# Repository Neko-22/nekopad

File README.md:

# Legally Distinct Catpad
Created for Hack Club Hackpad
## BOM
- 20x Cherry MX style switches
- 20x 1N418 THT Diodes
- 2x 4.7kOhm THT Resistors
- 1x I2C SSD1306 0.91" 128x32 OLED Display
- 1x XIAO RP2040 Microcontroller THT
- 1x Bottom Case (3D Print)
- 1x Top Case (3D Print)
- 1x Plate (Acryllic Laser Cut)
- 4x M3 screws
## Notes
This was hell ngl. I am absolutely *awful* at electronics design, and combine that with the joys of Linux software compatability regarding Fusion 360, I have lost so much sleep over this. I honestly think the firmware was the easiest part of this, and that's saying something.

10/10 experience would do again.

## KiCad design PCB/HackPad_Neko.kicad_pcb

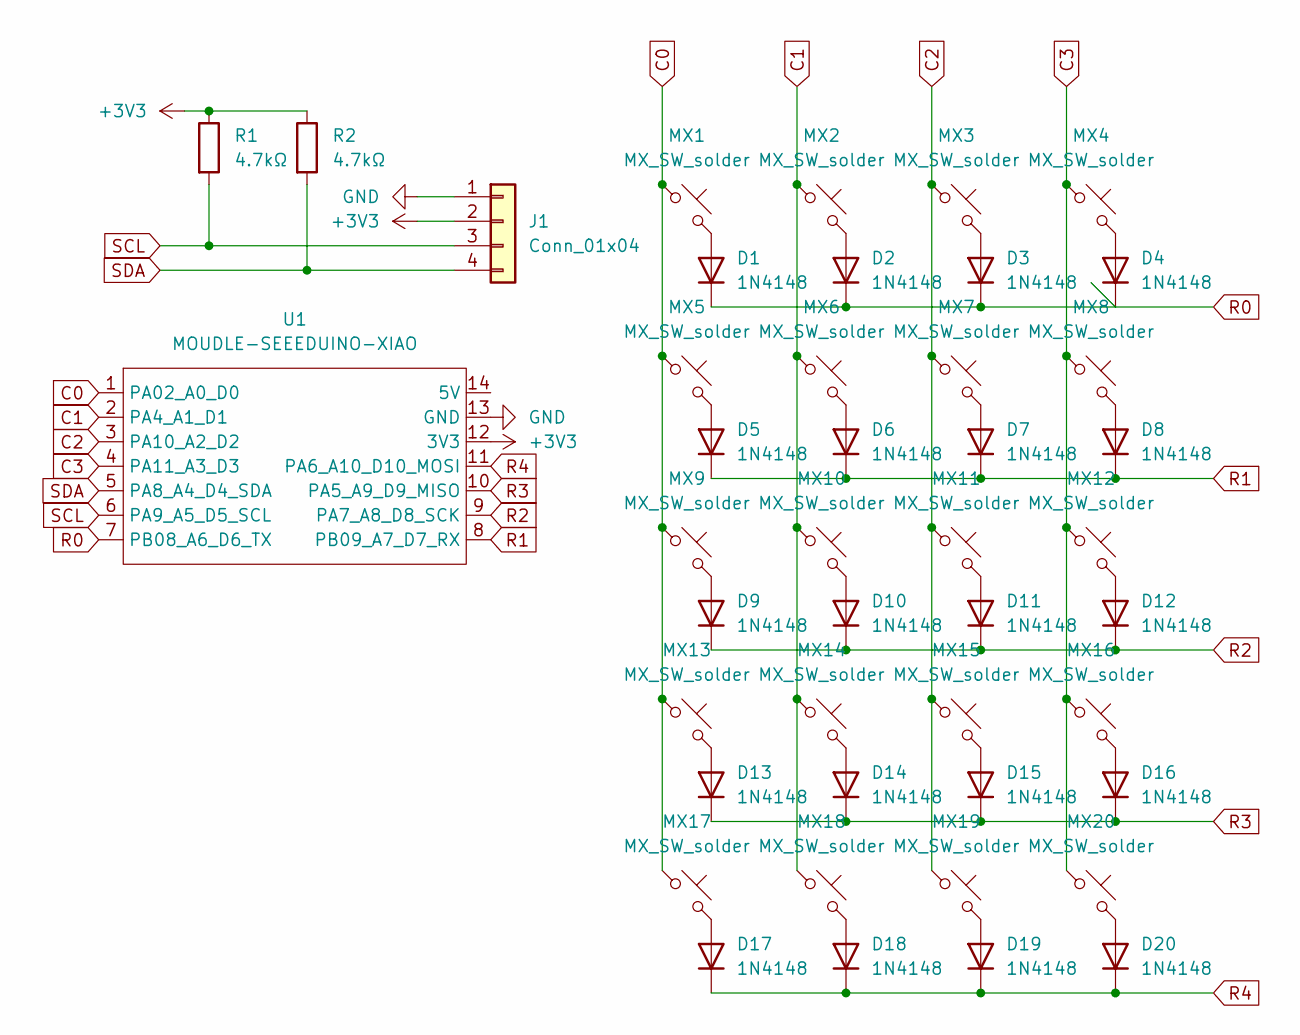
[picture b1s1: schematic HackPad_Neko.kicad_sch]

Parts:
D1, D2, D3, D4, D5, D6, D7, D8, D9, D10, D11, D12, D13, D14, D15, D16, D17, D18, D19, D20: 1N4148; D_DO-35_SOD27_P7.62mm_Horizontal
J1: Conn_01x04; SSD1306-0.91-OLED-4pin-128x32
MX1, MX2, MX3, MX4, MX5, MX6, MX7, MX8, MX9, MX10, MX11, MX12, MX13, MX14, MX15, MX16, MX17, MX18, MX19, MX20: MX_SW_solder; SW_Cherry_MX_1.00u_PCB
R1, R2: 4.7kΩ; R_Axial_DIN0204_L3.6mm_D1.6mm_P5.08mm_Horizontal
U1: MOUDLE-SEEEDUINO-XIAO; MOUDLE14P-2.54-21X17.8MM

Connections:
+3V3: J1.2, R1.1, R2.1, U1.12 (3V3)
C0: MX1.1, MX5.1, MX9.1, MX13.1, MX17.1, U1.1 (PA02_A0_D0)
C1: MX2.1, MX6.1, MX10.1, MX14.1, MX18.1, U1.2 (PA4_A1_D1)
C2: MX3.1, MX7.1, MX11.1, MX15.1, MX19.1, U1.3 (PA10_A2_D2)
C3: MX4.1, MX8.1, MX12.1, MX16.1, MX20.1, U1.4 (PA11_A3_D3)
GND: J1.1, U1.13 (GND)
unnamed: D1.2 (A), MX1.2
unnamed: D2.2 (A), MX2.2
unnamed: D3.2 (A), MX3.2
unnamed: D4.2 (A), MX4.2
unnamed: D5.2 (A), MX5.2
unnamed: D6.2 (A), MX6.2
unnamed: D7.2 (A), MX7.2
unnamed: D8.2 (A), MX8.2
unnamed: D9.2 (A), MX9.2
unnamed: D10.2 (A), MX10.2
unnamed: D11.2 (A), MX11.2
unnamed: D12.2 (A), MX12.2
unnamed: D13.2 (A), MX13.2
unnamed: D14.2 (A), MX14.2
unnamed: D15.2 (A), MX15.2
unnamed: D16.2 (A), MX16.2
unnamed: D17.2 (A), MX17.2
unnamed: D18.2 (A), MX18.2
unnamed: D19.2 (A), MX19.2
unnamed: D20.2 (A), MX20.2
R0: D1.1 (K), D2.1 (K), D3.1 (K), D4.1 (K), U1.7 (PB08_A6_D6_TX)
R1: D5.1 (K), D6.1 (K), D7.1 (K), D8.1 (K), U1.8 (PB09_A7_D7_RX)
R2: D9.1 (K), D10.1 (K), D11.1 (K), D12.1 (K), U1.9 (PA7_A8_D8_SCK)
R3: D13.1 (K), D14.1 (K), D15.1 (K), D16.1 (K), U1.10 (PA5_A9_D9_MISO)
R4: D17.1 (K), D18.1 (K), D19.1 (K), D20.1 (K), U1.11 (PA6_A10_D10_MOSI)
SCL: J1.3, R1.2, U1.6 (PA9_A5_D5_SCL)
SDA: J1.4, R2.2, U1.5 (PA8_A4_D4_SDA)

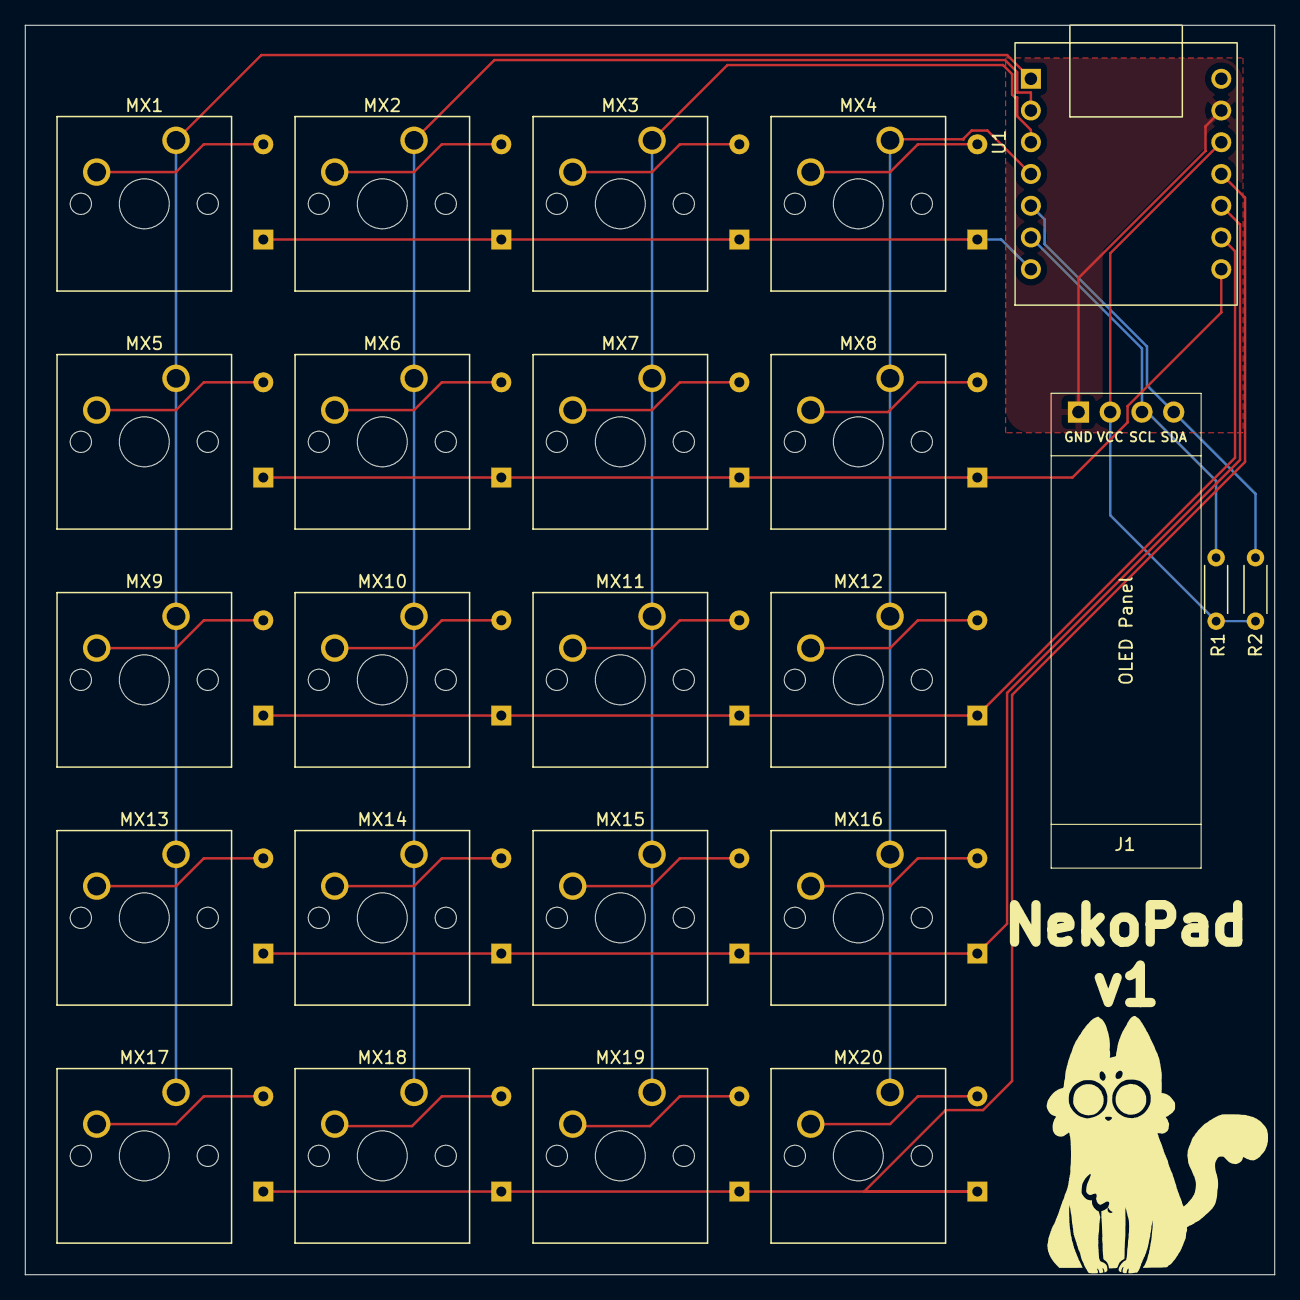
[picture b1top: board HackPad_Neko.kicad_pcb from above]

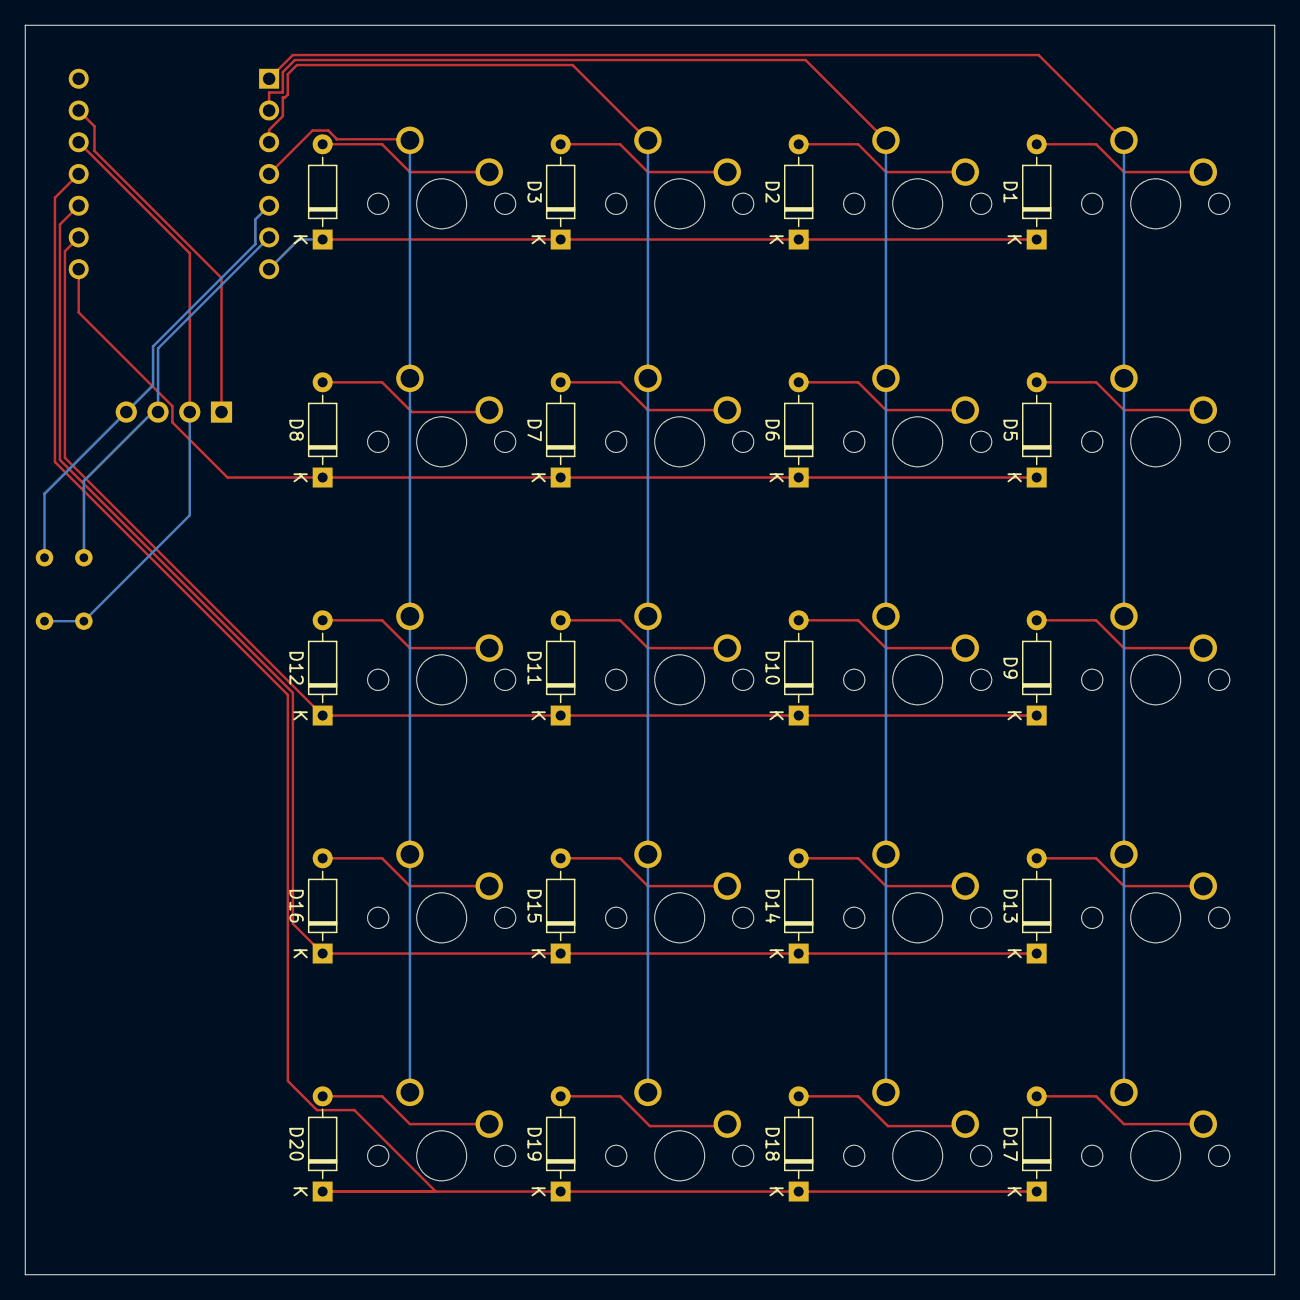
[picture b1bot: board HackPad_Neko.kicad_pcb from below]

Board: 2 copper layers, 100.0 x 100.0 mm, 44 parts (20 on the bottom side), 33 nets.

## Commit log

2024-10-05 yeet that s-
2024-10-05 Create a
2024-10-05 Rename HackPad_Neko-B_Cu.gbr to PCB/HackPad_Neko-B_Cu.gbr
2024-10-05 Rename HackPad_Neko-B_Mask.gbr to PCB/HackPad_Neko-B_Mask.gbr
2024-10-05 Rename HackPad_Neko-B_Paste.gbr to PCB/HackPad_Neko-B_Paste.gbr
2024-10-05 Rename HackPad_Neko-B_Silkscreen.gbr to PCB/HackPad_Neko-B_Silkscreen.gbr
2024-10-05 Rename HackPad_Neko-Edge_Cuts.gbr to PCB/HackPad_Neko-Edge_Cuts.gbr
2024-10-05 Rename HackPad_Neko-F_Cu.gbr to PCB/HackPad_Neko-F_Cu.gbr
2024-10-05 Rename HackPad_Neko-F_Mask.gbr to PCB/HackPad_Neko-F_Mask.gbr
2024-10-05 Rename HackPad_Neko-F_Paste.gbr to PCB/HackPad_Neko-F_Paste.gbr
2024-10-05 Rename HackPad_Neko-F_Silkscreen.gbr to PCB/HackPad_Neko-F_Silkscreen.gbr
2024-10-05 Rename HackPad_Neko-job.gbrjob to PCB/HackPad_Neko-job.gbrjob
2024-10-05 Rename HackPad_Neko.kicad_prl to PCB/HackPad_Neko.kicad_prl
2024-10-05 Rename HackPad_Neko.kicad_pcb to PCB/HackPad_Neko.kicad_pcb
2024-10-05 Rename HackPad_Neko.kicad_pro to PCB/HackPad_Neko.kicad_pro
2024-10-05 Rename HackPad_Neko.kicad_sch to PCB/HackPad_Neko.kicad_sch
2024-10-05 Rename fp-info-cache to PCB/fp-info-cache
2024-10-05 PCB take 2
2024-10-19 fix pcb issue
2024-10-19 firmware!!! yayayayayayayayay
2024-10-19 wrong dir name for firmware lol
2024-10-19 Update readme.md for firmware
2024-10-19 i dont know how to firmware,,,,,,
2024-10-21 case files
2024-10-21 gerber zip
2024-10-21 firmware file
2024-10-21 this is the 3mf
2024-10-21 update readme, hopefully final commit dear god
2024-10-21 whoops forgot CAD directory
2024-10-21 gerber dir
2024-10-21 update bom
2024-10-21 restore firmware
2024-10-21 p a i n
2024-10-22 aiowperghj-98awrh-90uwj4-9YUHW349-TU-98w24hyg-98aq3w4rg
2024-10-22 wrong image WRONG IMAGE
    i am going to commit eat soap
